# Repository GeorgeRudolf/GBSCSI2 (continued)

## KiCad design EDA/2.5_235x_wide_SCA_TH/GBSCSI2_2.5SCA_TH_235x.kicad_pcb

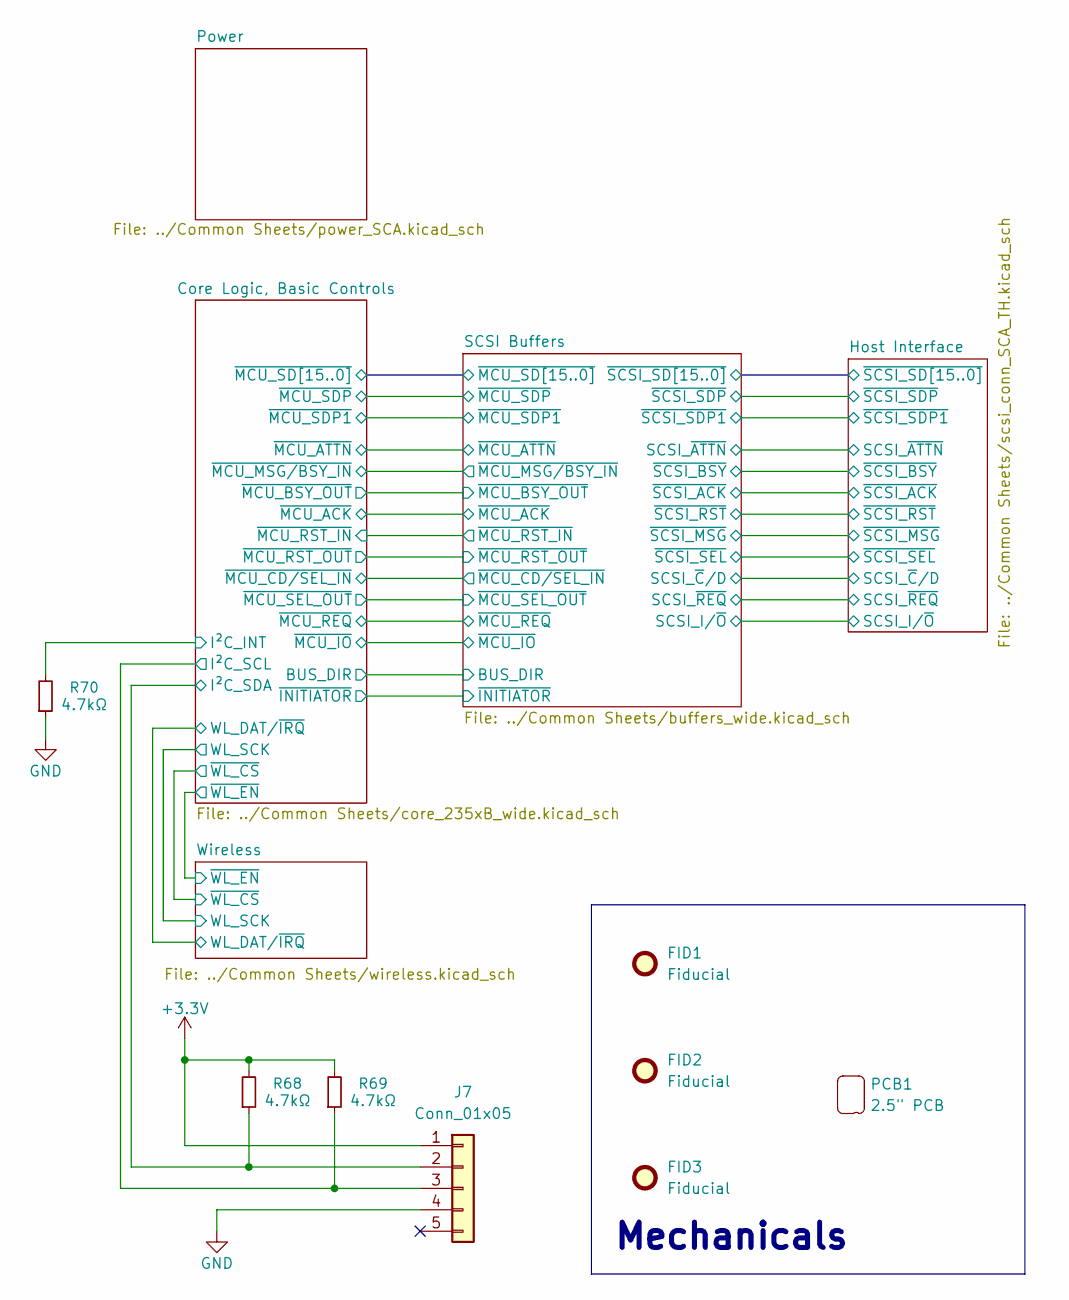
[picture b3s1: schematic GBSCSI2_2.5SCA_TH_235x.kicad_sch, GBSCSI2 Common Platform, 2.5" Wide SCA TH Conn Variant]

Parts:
FID1, FID2, FID3: Fiducial; Fiducial_0.5mm_Mask1mm; LCSC N/A
J7: Conn_01x05; PinSocket_1x05_P2.54mm_Vertical
PCB1: 2.5" PCB; GBSCSI2_2.5_PCB
R68, R69, R70: 4.7kΩ; R_0402_1005Metric; LCSC C25900

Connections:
+3.3V: J7.1, R68.2, R69.2; also elsewhere on the board
/Core Logic, Basic Controls/I²C_INT: R70.2; also elsewhere on the board
/Core Logic, Basic Controls/I²C_SCL: J7.3, R69.1; also elsewhere on the board
/Core Logic, Basic Controls/I²C_SDA: J7.2, R68.1; also elsewhere on the board
GND: J7.4, R70.1; also elsewhere on the board

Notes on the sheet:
Mechanicals

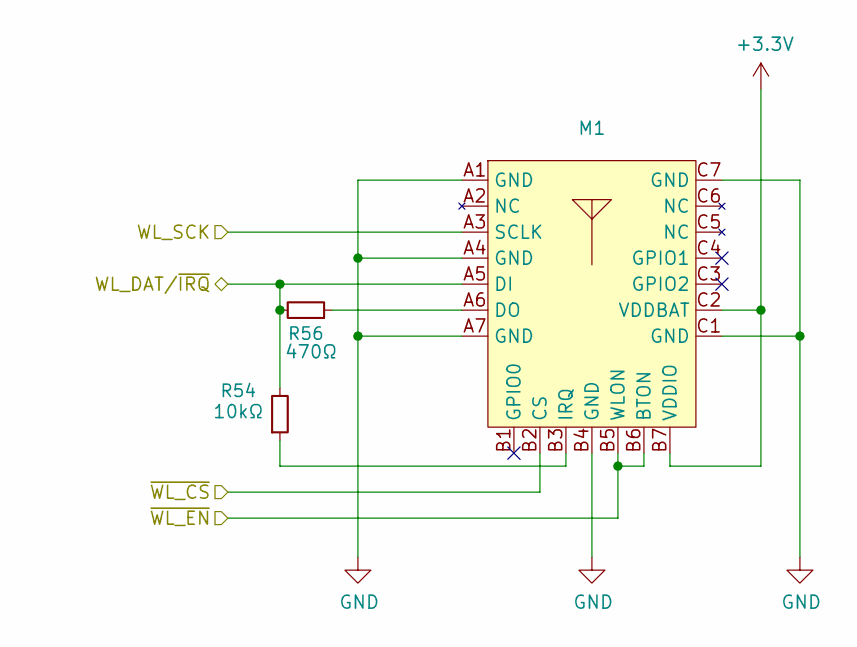
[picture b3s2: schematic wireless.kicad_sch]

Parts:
M1: RPi_RM2; LCSC N/A
R54: 10kΩ; R_0402_1005Metric; LCSC C25744
R56: 470Ω; R_0402_1005Metric

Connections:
+3.3V: M1.B7 (VDDIO), M1.C2 (VDDBAT); also elsewhere on the board
/Core Logic, Basic Controls/WL_DAT/~IRQ: M1.A5 (DI), R54.2, R56.2; also elsewhere on the board
/Core Logic, Basic Controls/WL_SCK: M1.A3 (SCLK); also elsewhere on the board
/Core Logic, Basic Controls/~WL_CS: M1.B2 (CS); also elsewhere on the board
/Core Logic, Basic Controls/~WL_EN: M1.B5 (WLON), M1.B6 (BTON); also elsewhere on the board
GND: M1.A1 (GND), M1.A4 (GND), M1.A7 (GND), M1.B4 (GND), M1.C1 (GND), M1.C7 (GND); also elsewhere on the board
unnamed: M1.A6 (DO), R56.1
unnamed: M1.B3 (IRQ), R54.1

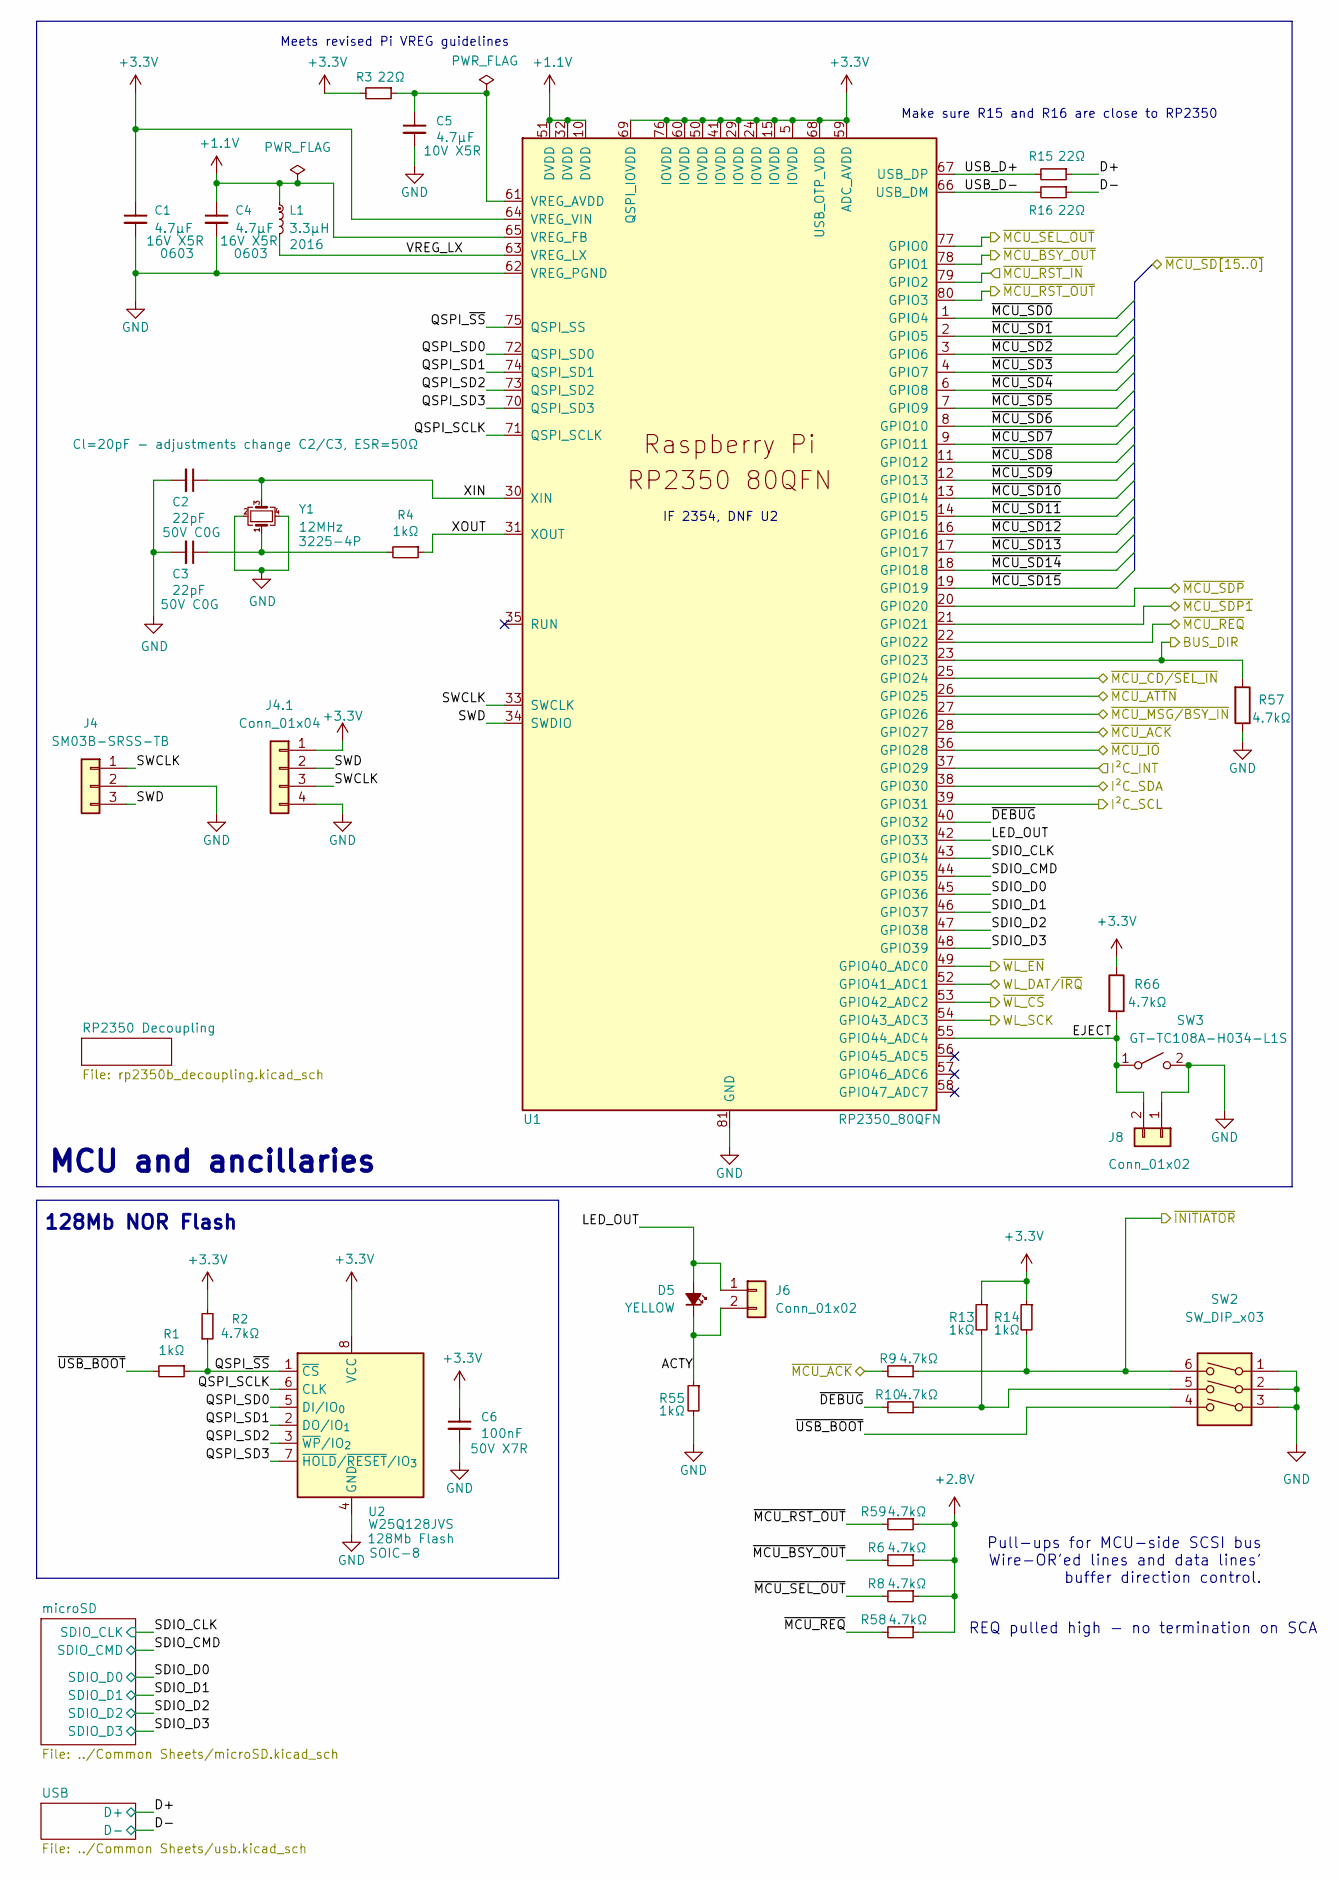
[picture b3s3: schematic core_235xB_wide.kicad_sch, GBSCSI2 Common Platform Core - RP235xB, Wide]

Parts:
C1, C4: 4.7μF; C_0603_1608Metric; LCSC C19666
C2, C3: 22pF; C_0402_1005Metric; LCSC C1555
C5: 4.7μF; C_0402_1005Metric; LCSC C23733
C6: 100nF; C_0402_1005Metric; LCSC C307331
D5: YELLOW; LED_0603_1608Metric; LCSC C72038
J4: SM03B-SRSS-TB; JST_SH_SM03B-SRSS-TB_1x03-1MP_P1.00mm_Horizontal; LCSC C160403
J4.1: Conn_01x04; PinHeader_1x04_P2.54mm_Vertical; LCSC N/A
J6, J8: Conn_01x02; PinHeader_1x02_P2.54mm_Vertical; LCSC N/A
L1: 3.3μH; L_Abracon_AOTA-B2016; LCSC C42411119
R1, R4: 1kΩ; R_0402_1005Metric; LCSC C11702
R2: 4.7kΩ; R_0402_1005Metric; LCSC C25900
R3, R15, R16: 22Ω; R_0402_1005Metric; LCSC C25092
R6, R8, R9, R10, R57, R58, R59, R66: 4.7kΩ; R_0603_1608Metric; LCSC C23162
R13, R14, R55: 1kΩ; R_0603_1608Metric; LCSC C21190
SW2: SW_DIP_x03; SW_DIP_SPSTx03_Slide_6.7x9.18mm_W8.61mm_P2.54mm_LowProfile; LCSC C2842910
SW3: GT-TC108A-H034-L1S; SW_Push_1P1T-MP_NO_Horizontal_Alps_SKRTLAE010
U1: RP2350_80QFN; RP2350-QFN-80-1EP_10x10_P0.4mm_EP3.4x3.4mm_ThermalVias; LCSC Part # C42415655
U2: W25Q128JVS; SOIC-8_5.23x5.23mm_P1.27mm; LCSC C97521
Y1: 12MHz; Crystal_SMD_3225-4Pin_3.2x2.5mm; LCSC C133334

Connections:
+1.1V: C4.1, L1.1, U1.10 (DVDD), U1.32 (DVDD), U1.51 (DVDD), U1.65 (VREG_FB); also elsewhere on the board
+2.8V: R6.1, R8.1, R58.1, R59.1; also elsewhere on the board
+3.3V: C1.1, C6.1, J4.1.1, R2.2, R3.2, R13.1, R14.1, R66.1, U1.5 (IOVDD), U1.15 (IOVDD), U1.24 (IOVDD), U1.29 (IOVDD), U1.41 (IOVDD), U1.50 (IOVDD), U1.59 (ADC_AVDD), U1.60 (IOVDD), U1.64 (VREG_VIN), U1.68 (USB_OTP_VDD), U1.69 (QSPI_IOVDD), U1.76 (IOVDD), U2.8 (VCC); also elsewhere on the board
/Core Logic, Basic Controls/ACTY: D5.1 (K), J6.2, R55.1
/Core Logic, Basic Controls/BUS_DIR: R57.2, U1.23 (GPIO23); also elsewhere on the board
/Core Logic, Basic Controls/D+: R15.1; also elsewhere on the board
/Core Logic, Basic Controls/D-: R16.1; also elsewhere on the board
/Core Logic, Basic Controls/EJECT: J8.2, R66.2, SW3.1 (A), U1.55 (GPIO44_ADC4)
/Core Logic, Basic Controls/I²C_INT: U1.37 (GPIO29); also elsewhere on the board
/Core Logic, Basic Controls/I²C_SCL: U1.39 (GPIO31); also elsewhere on the board
/Core Logic, Basic Controls/I²C_SDA: U1.38 (GPIO30); also elsewhere on the board
/Core Logic, Basic Controls/LED_OUT: D5.2 (A), J6.1, U1.42 (GPIO33)
/Core Logic, Basic Controls/QSPI_SCLK: U1.71 (QSPI_SCLK), U2.6 (CLK)
/Core Logic, Basic Controls/QSPI_SD0: U1.72 (QSPI_SD0), U2.5 (DI/IO_{0})
/Core Logic, Basic Controls/QSPI_SD1: U1.74 (QSPI_SD1), U2.2 (DO/IO_{1})
/Core Logic, Basic Controls/QSPI_SD2: U1.73 (QSPI_SD2), U2.3 (~WP/IO_{2})
/Core Logic, Basic Controls/QSPI_SD3: U1.70 (QSPI_SD3), U2.7 (~HOLD/~RESET/IO_{3})
/Core Logic, Basic Controls/QSPI_~SS: R1.1, R2.1, U1.75 (QSPI_SS), U2.1 (~CS)
/Core Logic, Basic Controls/SDIO_CLK: U1.43 (GPIO34); also elsewhere on the board
/Core Logic, Basic Controls/SDIO_CMD: U1.44 (GPIO35); also elsewhere on the board
/Core Logic, Basic Controls/SDIO_D0: U1.45 (GPIO36); also elsewhere on the board
/Core Logic, Basic Controls/SDIO_D1: U1.46 (GPIO37); also elsewhere on the board
/Core Logic, Basic Controls/SDIO_D2: U1.47 (GPIO38); also elsewhere on the board
/Core Logic, Basic Controls/SDIO_D3: U1.48 (GPIO39); also elsewhere on the board
/Core Logic, Basic Controls/SWCLK: J4.1, J4.1.3, U1.33 (SWCLK)
/Core Logic, Basic Controls/SWD: J4.3, J4.1.2, U1.34 (SWDIO)
/Core Logic, Basic Controls/USB_D+: R15.2, U1.67 (USB_DP)
/Core Logic, Basic Controls/USB_D-: R16.2, U1.66 (USB_DM)
/Core Logic, Basic Controls/VREG_LX: L1.2, U1.63 (VREG_LX)
/Core Logic, Basic Controls/WL_DAT/~IRQ: U1.52 (GPIO41_ADC1); also elsewhere on the board
/Core Logic, Basic Controls/WL_SCK: U1.54 (GPIO43_ADC3); also elsewhere on the board
/Core Logic, Basic Controls/XIN: C2.1, U1.30 (XIN), Y1.3
/Core Logic, Basic Controls/XOUT: R4.1, U1.31 (XOUT)
/Core Logic, Basic Controls/~DEBUG: R10.2, U1.40 (GPIO32)
/Core Logic, Basic Controls/~INITIATOR: R9.1, R14.2, SW2.6; also elsewhere on the board
/Core Logic, Basic Controls/~MCU_ACK: R9.2, U1.28 (GPIO27); also elsewhere on the board
/Core Logic, Basic Controls/~MCU_ATTN: U1.26 (GPIO25); also elsewhere on the board
/Core Logic, Basic Controls/~MCU_BSY_OUT: R6.2, U1.78 (GPIO1); also elsewhere on the board
/Core Logic, Basic Controls/~MCU_CD/SEL_IN: U1.25 (GPIO24); also elsewhere on the board
/Core Logic, Basic Controls/~MCU_IO: U1.36 (GPIO28); also elsewhere on the board
/Core Logic, Basic Controls/~MCU_MSG/BSY_IN: U1.27 (GPIO26); also elsewhere on the board
/Core Logic, Basic Controls/~MCU_REQ: R58.2, U1.22 (GPIO22); also elsewhere on the board
/Core Logic, Basic Controls/~MCU_RST_IN: U1.79 (GPIO2); also elsewhere on the board
/Core Logic, Basic Controls/~MCU_RST_OUT: R59.2, U1.80 (GPIO3); also elsewhere on the board
/Core Logic, Basic Controls/~MCU_SD0: U1.1 (GPIO4); also elsewhere on the board
/Core Logic, Basic Controls/~MCU_SD1: U1.2 (GPIO5); also elsewhere on the board
/Core Logic, Basic Controls/~MCU_SD2: U1.3 (GPIO6); also elsewhere on the board
/Core Logic, Basic Controls/~MCU_SD3: U1.4 (GPIO7); also elsewhere on the board
/Core Logic, Basic Controls/~MCU_SD4: U1.6 (GPIO8); also elsewhere on the board
/Core Logic, Basic Controls/~MCU_SD5: U1.7 (GPIO9); also elsewhere on the board
/Core Logic, Basic Controls/~MCU_SD6: U1.8 (GPIO10); also elsewhere on the board
/Core Logic, Basic Controls/~MCU_SD7: U1.9 (GPIO11); also elsewhere on the board
/Core Logic, Basic Controls/~MCU_SD8: U1.11 (GPIO12); also elsewhere on the board
/Core Logic, Basic Controls/~MCU_SD9: U1.12 (GPIO13); also elsewhere on the board
/Core Logic, Basic Controls/~MCU_SD10: U1.13 (GPIO14); also elsewhere on the board
/Core Logic, Basic Controls/~MCU_SD11: U1.14 (GPIO15); also elsewhere on the board
/Core Logic, Basic Controls/~MCU_SD12: U1.16 (GPIO16); also elsewhere on the board
/Core Logic, Basic Controls/~MCU_SD13: U1.17 (GPIO17); also elsewhere on the board
/Core Logic, Basic Controls/~MCU_SD14: U1.18 (GPIO18); also elsewhere on the board
/Core Logic, Basic Controls/~MCU_SD15: U1.19 (GPIO19); also elsewhere on the board
/Core Logic, Basic Controls/~MCU_SDP1: U1.21 (GPIO21)
/Core Logic, Basic Controls/~MCU_SDP: U1.20 (GPIO20)
/Core Logic, Basic Controls/~MCU_SEL_OUT: R8.2, U1.77 (GPIO0); also elsewhere on the board
/Core Logic, Basic Controls/~USB_BOOT: R1.2, SW2.4
/Core Logic, Basic Controls/~WL_CS: U1.53 (GPIO42_ADC2); also elsewhere on the board
/Core Logic, Basic Controls/~WL_EN: U1.49 (GPIO40_ADC0); also elsewhere on the board
GND: C1.2, C2.2, C3.2, C4.2, C5.2, C6.2, J4.2, J4.1.4, J8.1, R55.2, R57.1, SW2.1, SW2.2, SW2.3, SW3.2 (B), U1.62 (VREG_PGND), U1.81 (GND), U2.4 (GND), Y1.2, Y1.4; also elsewhere on the board
unnamed: C3.1, R4.2, Y1.1
unnamed: R10.1, R13.2, SW2.5
unnamed: C5.1, R3.1, U1.61 (VREG_AVDD)

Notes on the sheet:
128Mb NOR Flash
Pull-ups for MCU-side SCSI bus Wire-OR'ed lines and data lines' buffer direction control.
IF 2354, DNF U2
MCU and ancillaries
REQ pulled high - no termination on SCA
Make sure R15 and R16 are close to RP2350
Meets revised Pi VREG guidelines

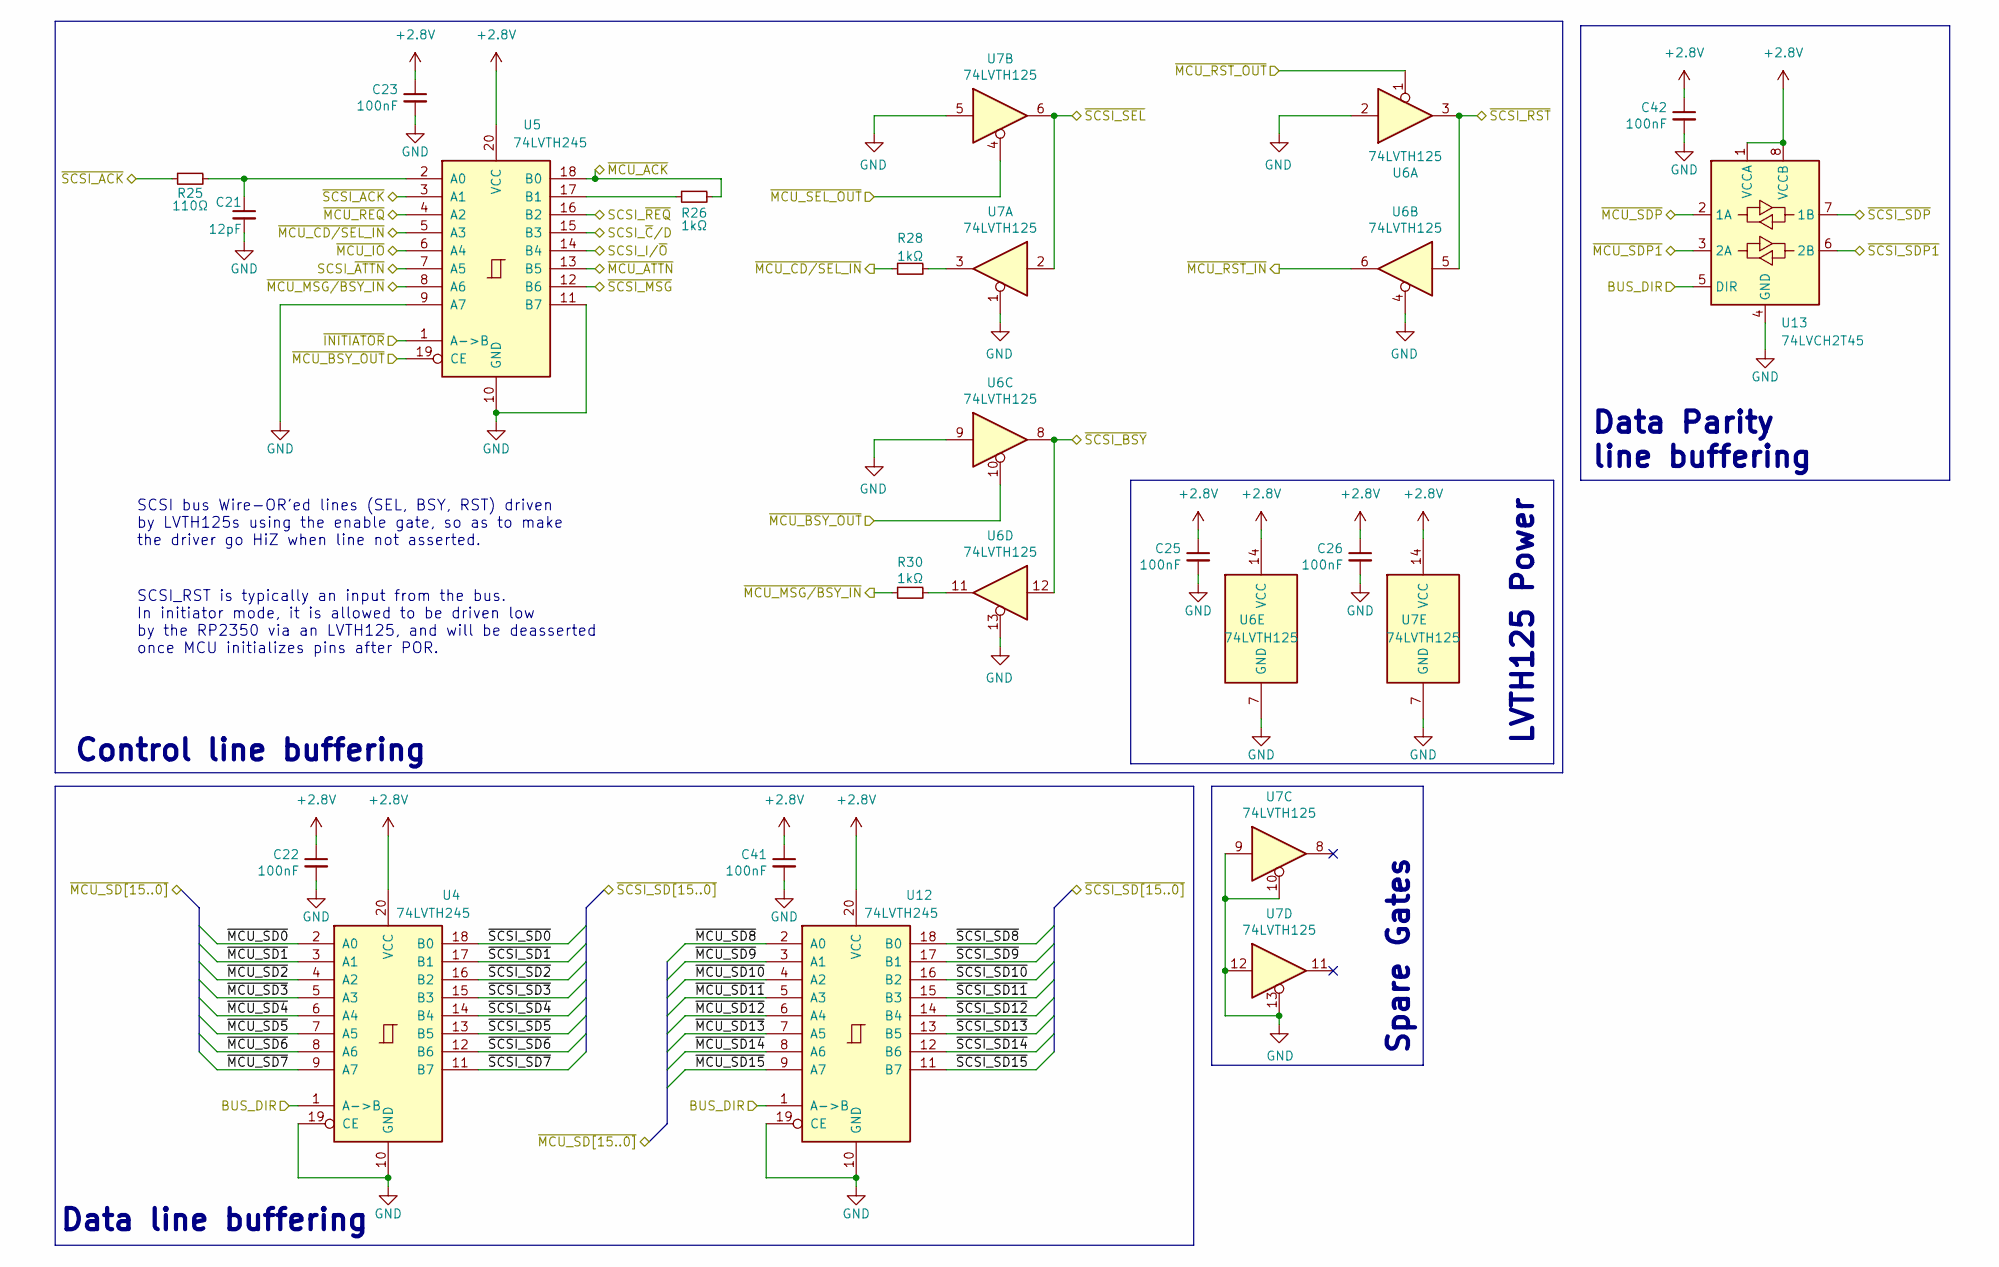
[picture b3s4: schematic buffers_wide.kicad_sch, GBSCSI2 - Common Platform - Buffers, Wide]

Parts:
C21: 12pF; C_0603_1608Metric; LCSC C38523
C22, C23, C25, C26, C41: 100nF; C_0603_1608Metric; LCSC C14663
C42: 100nF; C_0402_1005Metric; LCSC C1525
R25: 110Ω; R_0603_1608Metric; LCSC C22781
R26, R28, R30: 1kΩ; R_0603_1608Metric; LCSC C21190
U4, U5, U12: 74LVTH245; SSOP-20_5.3x7.2mm_P0.65mm; LCSC C2652121
U6, U7: 74LVTH125; TSSOP-14_4.4x5mm_P0.65mm; LCSC C7042
U13: 74LVCH2T45; LCSC C5916231

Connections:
+2.8V: C22.1, C23.1, C25.1, C26.1, C41.1, C42.1, U4.20 (VCC), U5.20 (VCC), U6.14 (VCC), U7.14 (VCC), U12.20 (VCC), U13.1 (VCCA), U13.8 (VCCB); also elsewhere on the board
/Core Logic, Basic Controls/BUS_DIR: U4.1 (A->B), U12.1 (A->B), U13.5 (DIR); also elsewhere on the board
/Core Logic, Basic Controls/~INITIATOR: U5.1 (A->B); also elsewhere on the board
/Core Logic, Basic Controls/~MCU_ACK: R26.2, U5.18 (B0); also elsewhere on the board
/Core Logic, Basic Controls/~MCU_ATTN: U5.13 (B5); also elsewhere on the board
/Core Logic, Basic Controls/~MCU_BSY_OUT: U5.19 (CE), U6.10; also elsewhere on the board
/Core Logic, Basic Controls/~MCU_CD/SEL_IN: R28.1, U5.5 (A3); also elsewhere on the board
/Core Logic, Basic Controls/~MCU_IO: U5.6 (A4); also elsewhere on the board
/Core Logic, Basic Controls/~MCU_MSG/BSY_IN: R30.1, U5.8 (A6); also elsewhere on the board
/Core Logic, Basic Controls/~MCU_REQ: U5.4 (A2); also elsewhere on the board
/Core Logic, Basic Controls/~MCU_RST_IN: U6.6; also elsewhere on the board
/Core Logic, Basic Controls/~MCU_RST_OUT: U6.1; also elsewhere on the board
/Core Logic, Basic Controls/~MCU_SD0: U4.2 (A0); also elsewhere on the board
/Core Logic, Basic Controls/~MCU_SD1: U4.3 (A1); also elsewhere on the board
/Core Logic, Basic Controls/~MCU_SD2: U4.4 (A2); also elsewhere on the board
/Core Logic, Basic Controls/~MCU_SD3: U4.5 (A3); also elsewhere on the board
/Core Logic, Basic Controls/~MCU_SD4: U4.6 (A4); also elsewhere on the board
/Core Logic, Basic Controls/~MCU_SD5: U4.7 (A5); also elsewhere on the board
/Core Logic, Basic Controls/~MCU_SD6: U4.8 (A6); also elsewhere on the board
/Core Logic, Basic Controls/~MCU_SD7: U4.9 (A7); also elsewhere on the board
/Core Logic, Basic Controls/~MCU_SD8: U12.2 (A0); also elsewhere on the board
/Core Logic, Basic Controls/~MCU_SD9: U12.3 (A1); also elsewhere on the board
/Core Logic, Basic Controls/~MCU_SD10: U12.4 (A2); also elsewhere on the board
/Core Logic, Basic Controls/~MCU_SD11: U12.5 (A3); also elsewhere on the board
/Core Logic, Basic Controls/~MCU_SD12: U12.6 (A4); also elsewhere on the board
/Core Logic, Basic Controls/~MCU_SD13: U12.7 (A5); also elsewhere on the board
/Core Logic, Basic Controls/~MCU_SD14: U12.8 (A6); also elsewhere on the board
/Core Logic, Basic Controls/~MCU_SD15: U12.9 (A7); also elsewhere on the board
/Core Logic, Basic Controls/~MCU_SEL_OUT: U7.4; also elsewhere on the board
/Host Interface/SCSI_I/~O: U5.14 (B4); also elsewhere on the board
/Host Interface/SCSI_~ATTN: U5.7 (A5); also elsewhere on the board
/Host Interface/SCSI_~C/D: U5.15 (B3); also elsewhere on the board
/Host Interface/SCSI_~REQ: U5.16 (B2); also elsewhere on the board
/Host Interface/~SCSI_ACK: R25.1, U5.3 (A1); also elsewhere on the board
/Host Interface/~SCSI_BSY: U6.8, U6.12; also elsewhere on the board
/Host Interface/~SCSI_MSG: U5.12 (B6); also elsewhere on the board
/Host Interface/~SCSI_RST: U6.3, U6.5; also elsewhere on the board
/Host Interface/~SCSI_SD0: U4.18 (B0); also elsewhere on the board
/Host Interface/~SCSI_SD1: U4.17 (B1); also elsewhere on the board
/Host Interface/~SCSI_SD2: U4.16 (B2); also elsewhere on the board
/Host Interface/~SCSI_SD3: U4.15 (B3); also elsewhere on the board
/Host Interface/~SCSI_SD4: U4.14 (B4); also elsewhere on the board
/Host Interface/~SCSI_SD5: U4.13 (B5); also elsewhere on the board
/Host Interface/~SCSI_SD6: U4.12 (B6); also elsewhere on the board
/Host Interface/~SCSI_SD7: U4.11 (B7); also elsewhere on the board
/Host Interface/~SCSI_SD8: U12.18 (B0); also elsewhere on the board
/Host Interface/~SCSI_SD9: U12.17 (B1); also elsewhere on the board
/Host Interface/~SCSI_SD10: U12.16 (B2); also elsewhere on the board
/Host Interface/~SCSI_SD11: U12.15 (B3); also elsewhere on the board
/Host Interface/~SCSI_SD12: U12.14 (B4); also elsewhere on the board
/Host Interface/~SCSI_SD13: U12.13 (B5); also elsewhere on the board
/Host Interface/~SCSI_SD14: U12.12 (B6); also elsewhere on the board
/Host Interface/~SCSI_SD15: U12.11 (B7); also elsewhere on the board
/Host Interface/~SCSI_SEL: U7.2, U7.6; also elsewhere on the board
GND: C21.2, C22.2, C23.2, C25.2, C26.2, C41.2, C42.2, U4.10 (GND), U4.19 (CE), U5.9 (A7), U5.10 (GND), U5.11 (B7), U6.2, U6.4, U6.7 (GND), U6.9, U6.13, U7.1, U7.5, U7.7 (GND), U7.9, U7.10, U7.12, U7.13, U12.10 (GND), U12.19 (CE), U13.4 (GND); also elsewhere on the board
unnamed: R28.2, U7.3
unnamed: R30.2, U6.11
unnamed: C21.1, R25.2, U5.2 (A0)
unnamed: R26.1, U5.17 (B1)

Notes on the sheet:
Control line buffering
SCSI_RST is typically an input from the bus. In initiator mode, it is allowed to be driven low by the RP2350 via an LVTH125, and will be deasserted once MCU initializes pins after POR.
LVTH125 Power
SCSI bus Wire-OR'ed lines (SEL, BSY, RST) driven by LVTH125s using the enable gate, so as to make the driver go HiZ when line not asserted.
Spare Gates
Data Parity line buffering
Data line buffering

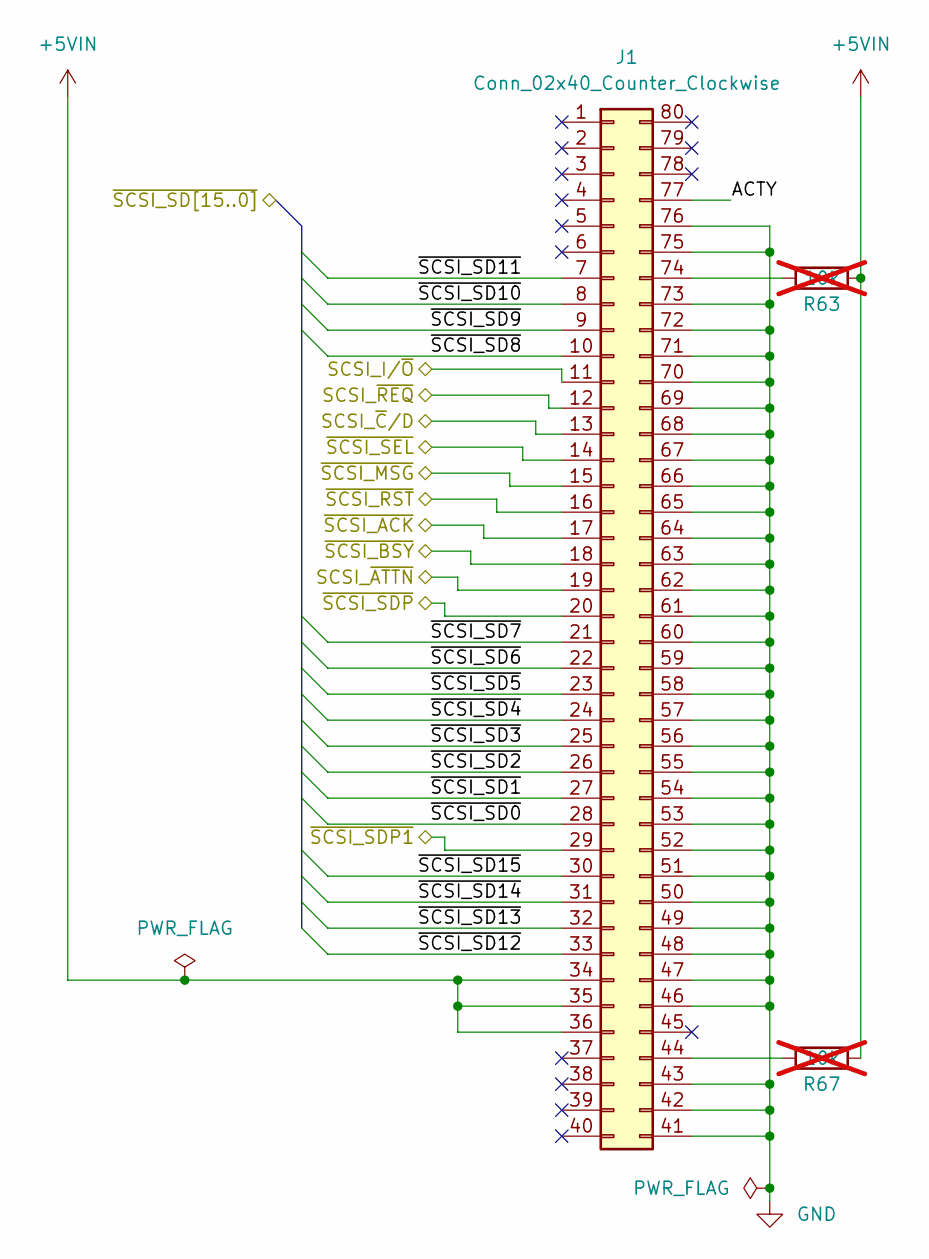
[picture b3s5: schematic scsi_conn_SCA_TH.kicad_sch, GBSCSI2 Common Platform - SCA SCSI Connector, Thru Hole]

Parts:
J1: Conn_02x40_Counter_Clockwise; CHAMPII_80
R63, R67: 10k; R_0603_1608Metric; LCSC C25804; not fitted

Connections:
+5VIN: J1.34, J1.35, J1.36, R63.2, R67.2; also elsewhere on the board
/Host Interface/ACTY: J1.77
/Host Interface/SCSI_I/~O: J1.11; also elsewhere on the board
/Host Interface/SCSI_~ATTN: J1.19; also elsewhere on the board
/Host Interface/SCSI_~C/D: J1.13; also elsewhere on the board
/Host Interface/SCSI_~REQ: J1.12; also elsewhere on the board
/Host Interface/~SCSI_ACK: J1.17; also elsewhere on the board
/Host Interface/~SCSI_BSY: J1.18; also elsewhere on the board
/Host Interface/~SCSI_MSG: J1.15; also elsewhere on the board
/Host Interface/~SCSI_RST: J1.16; also elsewhere on the board
/Host Interface/~SCSI_SD0: J1.28; also elsewhere on the board
/Host Interface/~SCSI_SD1: J1.27; also elsewhere on the board
/Host Interface/~SCSI_SD2: J1.26; also elsewhere on the board
/Host Interface/~SCSI_SD3: J1.25; also elsewhere on the board
/Host Interface/~SCSI_SD4: J1.24; also elsewhere on the board
/Host Interface/~SCSI_SD5: J1.23; also elsewhere on the board
/Host Interface/~SCSI_SD6: J1.22; also elsewhere on the board
/Host Interface/~SCSI_SD7: J1.21; also elsewhere on the board
/Host Interface/~SCSI_SD8: J1.10; also elsewhere on the board
/Host Interface/~SCSI_SD9: J1.9; also elsewhere on the board
/Host Interface/~SCSI_SD10: J1.8; also elsewhere on the board
/Host Interface/~SCSI_SD11: J1.7; also elsewhere on the board
/Host Interface/~SCSI_SD12: J1.33; also elsewhere on the board
/Host Interface/~SCSI_SD13: J1.32; also elsewhere on the board
/Host Interface/~SCSI_SD14: J1.31; also elsewhere on the board
/Host Interface/~SCSI_SD15: J1.30; also elsewhere on the board
/Host Interface/~SCSI_SDP1: J1.29
/Host Interface/~SCSI_SDP: J1.20
/Host Interface/~SCSI_SEL: J1.14; also elsewhere on the board
GND: J1.41, J1.42, J1.43, J1.46, J1.47, J1.48, J1.49, J1.50, J1.51, J1.52, J1.53, J1.54, J1.55, J1.56, J1.57, J1.58, J1.59, J1.60, J1.61, J1.62, J1.63, J1.64, J1.65, J1.66, J1.67, J1.68, J1.69, J1.70, J1.71, J1.72, J1.73, J1.75, J1.76; also elsewhere on the board
unnamed: J1.44, R67.1
unnamed: J1.74, R63.1

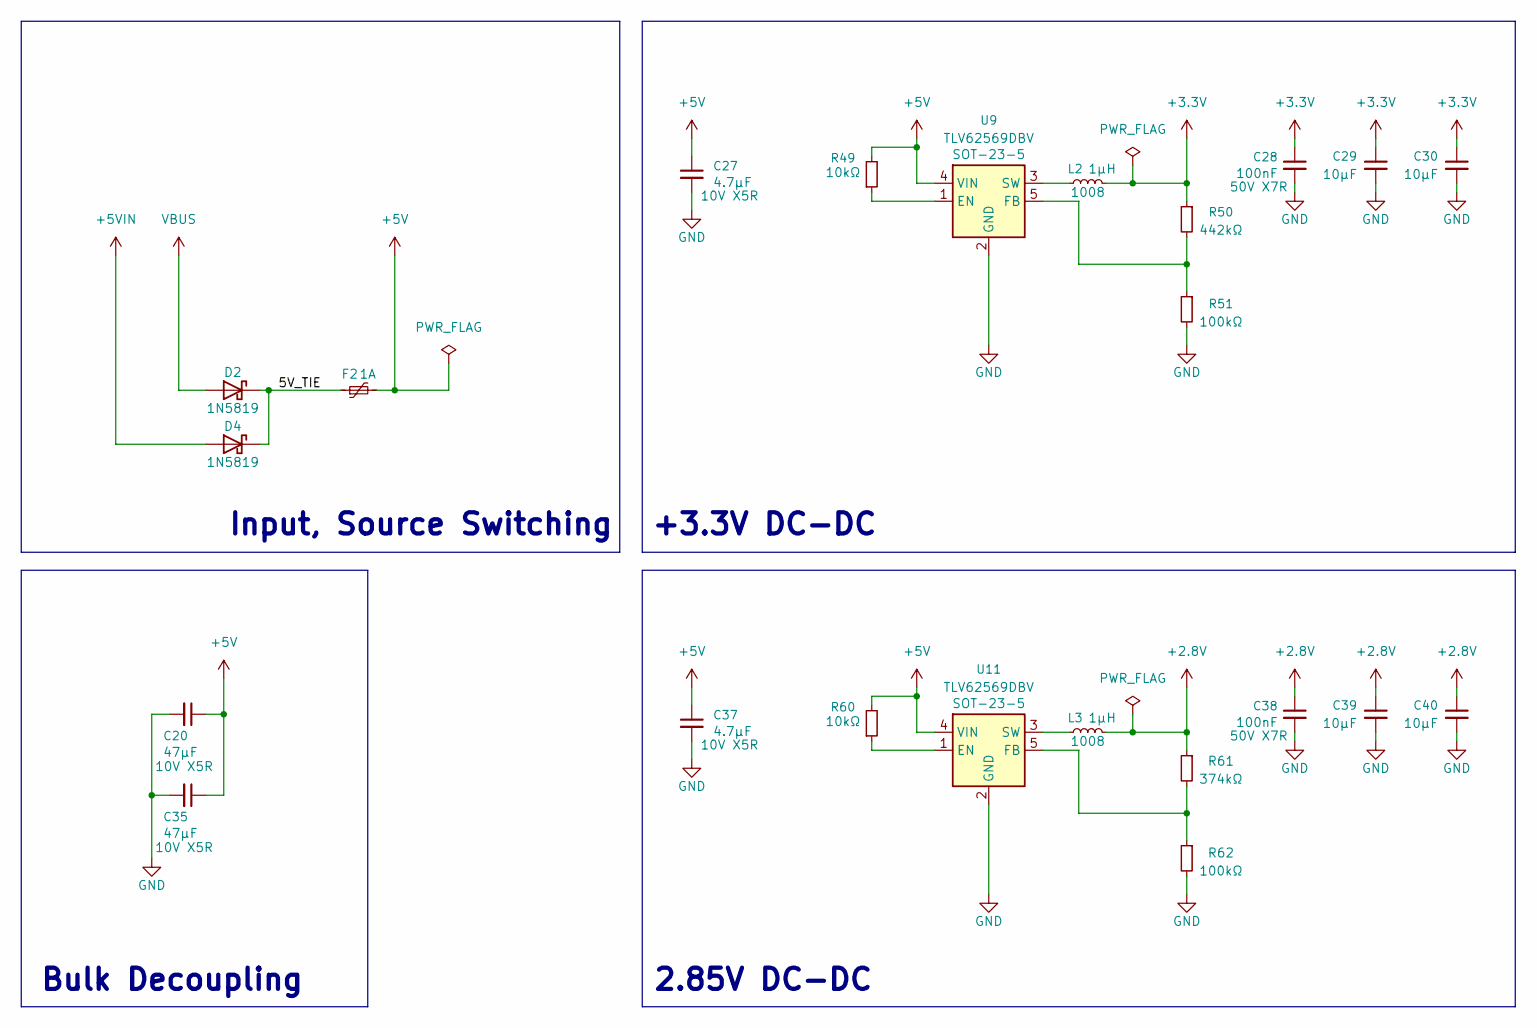
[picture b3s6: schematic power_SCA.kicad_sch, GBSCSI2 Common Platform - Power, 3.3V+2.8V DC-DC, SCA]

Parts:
C20, C35: 47μF; C_1206_3216Metric; LCSC C96123
C27, C37: 4.7μF; C_0402_1005Metric; LCSC C23733
C28, C38: 100nF; C_0402_1005Metric; LCSC C307331
C29, C30, C39, C40: 10μF; C_0603_1608Metric; LCSC C96446
D2, D4: 1N5819; D_SOD-123; LCSC C191023
F2: 1A; Fuse_0805_2012Metric; LCSC C468888
L2, L3: 1μH; L_1008_2520Metric; LCSC C5832356
R49, R60: 10kΩ; R_0402_1005Metric; LCSC C25744
R50: 442kΩ; R_0402_1005Metric; LCSC C5101
R51, R62: 100kΩ; R_0402_1005Metric; LCSC C25741
R61: 374kΩ; R_0402_1005Metric; LCSC C25781
U9, U11: TLV62569DBV; SOT-23-5; LCSC C141836

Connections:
+2.8V: C38.1, C39.1, C40.1, L3.2, R61.1; also elsewhere on the board
+3.3V: C28.1, C29.1, C30.1, L2.2, R50.1; also elsewhere on the board
+5V: C20.1, C27.1, C35.1, C37.1, F2.2, R49.2, R60.2, U9.4 (VIN), U11.4 (VIN)
+5VIN: D4.2 (A); also elsewhere on the board
/Power/5V_TIE: D2.1 (K), D4.1 (K), F2.1
GND: C20.2, C27.2, C28.2, C29.2, C30.2, C35.2, C37.2, C38.2, C39.2, C40.2, R51.2, R62.2, U9.2 (GND), U11.2 (GND); also elsewhere on the board
unnamed: R49.1, U9.1 (EN)
unnamed: R50.2, R51.1, U9.5 (FB)
unnamed: L2.1, U9.3 (SW)
unnamed: R60.1, U11.1 (EN)
unnamed: R61.2, R62.1, U11.5 (FB)
unnamed: L3.1, U11.3 (SW)
VBUS: D2.2 (A); also elsewhere on the board

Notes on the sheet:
+3.3V DC-DC
Bulk Decoupling
Input, Source Switching
2.85V DC-DC

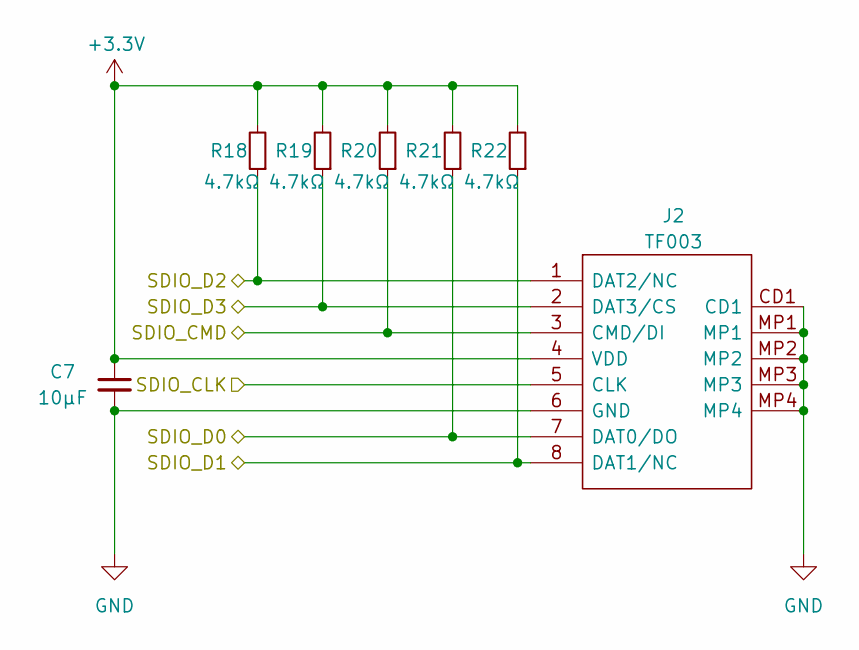
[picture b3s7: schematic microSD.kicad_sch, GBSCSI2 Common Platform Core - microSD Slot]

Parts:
C7: 10μF; C_0603_1608Metric; LCSC C96446
J2: TF003; TF01A; LCSC C5155563
R18, R19, R20, R21, R22: 4.7kΩ; R_0603_1608Metric; LCSC C23162

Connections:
+3.3V: C7.1, J2.4 (VDD), R18.2, R19.2, R20.2, R21.2, R22.2; also elsewhere on the board
/Core Logic, Basic Controls/SDIO_CLK: J2.5 (CLK); also elsewhere on the board
/Core Logic, Basic Controls/SDIO_CMD: J2.3 (CMD/DI), R20.1; also elsewhere on the board
/Core Logic, Basic Controls/SDIO_D0: J2.7 (DAT0/DO), R21.1; also elsewhere on the board
/Core Logic, Basic Controls/SDIO_D1: J2.8 (DAT1/NC), R22.1; also elsewhere on the board
/Core Logic, Basic Controls/SDIO_D2: J2.1 (DAT2/NC), R18.1; also elsewhere on the board
/Core Logic, Basic Controls/SDIO_D3: J2.2 (DAT3/CS), R19.1; also elsewhere on the board
GND: C7.2, J2.6 (GND), J2.CD1, J2.MP1, J2.MP2, J2.MP3, J2.MP4; also elsewhere on the board

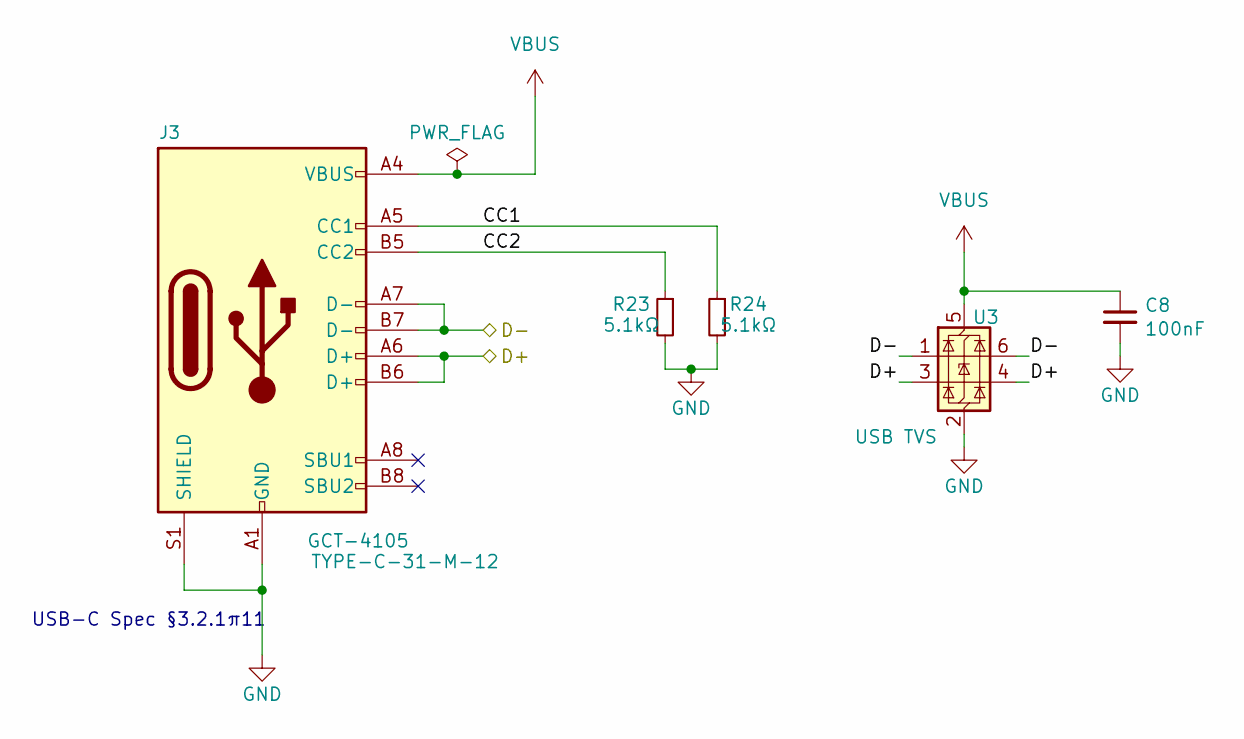
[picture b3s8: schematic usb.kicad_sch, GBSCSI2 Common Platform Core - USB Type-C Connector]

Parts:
C8: 100nF; C_0402_1005Metric; LCSC C307331
J3: GCT-4105; USB_C_Receptacle_HRO_TYPE-C-31-M-12; LCSC C2927038
R23, R24: 5.1kΩ; R_0402_1005Metric; LCSC C25905
U3: USB TVS; SOT-23-6; LCSC C2827654

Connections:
/Core Logic, Basic Controls/D+: J3.A6 (D+), J3.B6 (D+), U3.3 (I/O2), U3.4 (I/O2); also elsewhere on the board
/Core Logic, Basic Controls/D-: J3.A7 (D-), J3.B7 (D-), U3.1 (I/O1), U3.6 (I/O1); also elsewhere on the board
/Core Logic, Basic Controls/USB/CC1: J3.A5 (CC1), R24.1
/Core Logic, Basic Controls/USB/CC2: J3.B5 (CC2), R23.1
GND: C8.2, J3.A1 (GND), J3.A12 (GND), J3.B1 (GND), J3.B12 (GND), J3.S1 (SHIELD), R23.2, R24.2, U3.2 (GND); also elsewhere on the board
VBUS: C8.1, J3.A4 (VBUS), J3.A9 (VBUS), J3.B4 (VBUS), J3.B9 (VBUS), U3.5 (VBUS); also elsewhere on the board

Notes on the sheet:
USB-C Spec §3.2.1¶11
